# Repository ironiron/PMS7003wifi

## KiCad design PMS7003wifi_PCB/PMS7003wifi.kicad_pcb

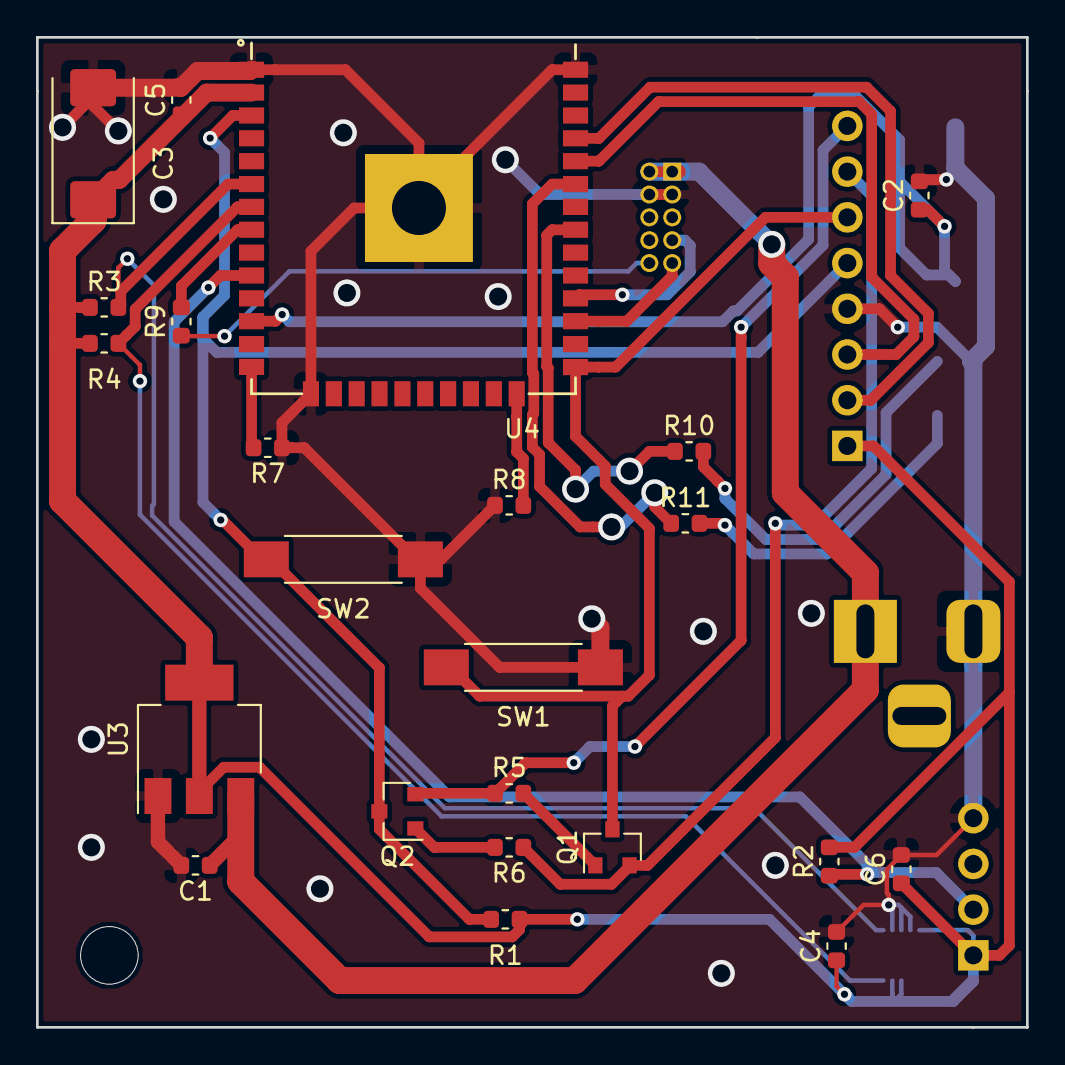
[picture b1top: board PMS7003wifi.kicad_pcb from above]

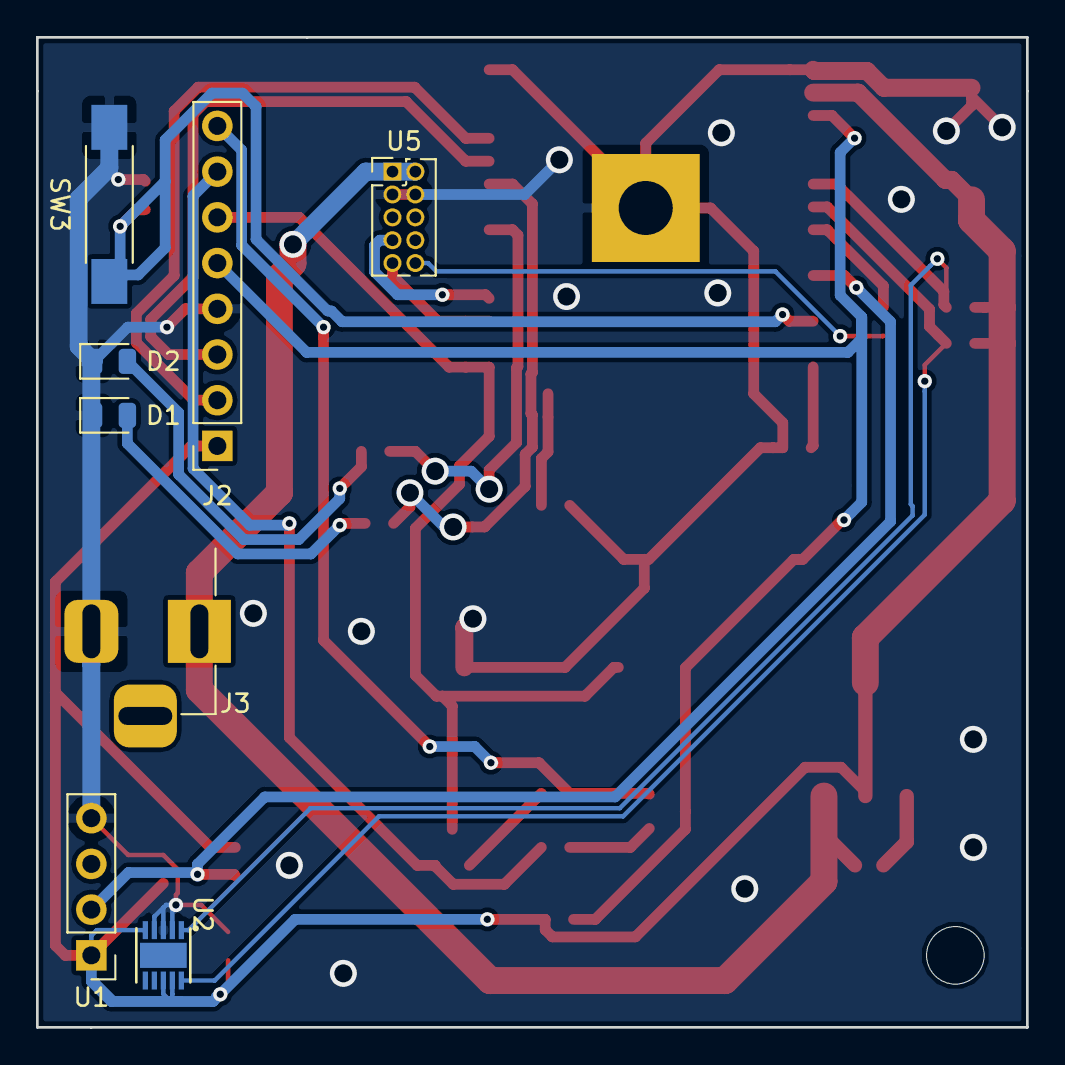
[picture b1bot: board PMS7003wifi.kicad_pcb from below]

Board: 2 copper layers, 55.0 x 55.0 mm, 32 parts (8 on the bottom side), 25 nets.

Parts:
 : MountingHole_3.2mm_M3
C1: 10u; C_0603_1608Metric
C2, C4, C5, C6: 100n; C_0603_1608Metric
C3: 470u; CP_EIA-7343-31_Kemet-D
D1, D2: RED; LED_0805_2012Metric
J2: Conn_01x06; PinSocket_1x08_P2.54mm_Vertical
J3: Jack-DC; BarrelJack_Horizontal
Q1, Q2: BC817; SOT-23
R1, R5, R6, R7, R8: 10K; R_0603_1608Metric
R2: 5K; R_0603_1608Metric
R3, R4: 2K2; R_0603_1608Metric
R9, R10, R11: 470; R_0603_1608Metric
SW1: DOWNLOAD_FLASH; SW_SPST_REED_CT05-XXXX-G1
SW2: EN(RST); SW_SPST_REED_CT05-XXXX-G1
SW3: wifi; SW_SPST_REED_CT05-XXXX-G1
U1: DHT11; PinHeader_1x04_P2.54mm_Vertical
U2: Si7013-A20; DFN10
U3: AP1117-33; SOT-223-3_TabPin2
U4: ESP32-WROOM; ESP32
U5: PMS7003; PinHeader_2x05_P1.27mm_Vertical

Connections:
+3V3: C3.1, C4.1, C5.1, C6.1, J2.1, R1.2, R2.2, R3.1, R4.1, U1.1, U2.5, U2.8, U2.9, U3.2, U4.2
+5V: C1.1, J3.1, U3.3, U5.1, U5.2
/DOWNLOAD_32: J2.6, Q1.3, SW1.1, U4.25
/DTR: J2.7, Q1.2, R6.1
/EN_32: J2.5, Q2.3, R1.1, SW2.1, U4.3
/MCU_RX: U4.27, U5.9
/MCU_TX: U4.28, U5.7
/ONEWIRE: R2.1, U1.2, U4.10
/RTS: J2.8, Q2.2, R5.1
/RX0_32: J2.3, U4.34
/SCLK: R4.2, U2.10, U4.7
/SDA: R3.2, U2.1, U4.6
/SET: R9.2, U4.8
/TX0_32: J2.2, U4.35
GND: C1.2, C2.2, C3.2, C4.2, C5.2, C6.2, D1.1, D2.1, J2.4, J3.2, R7.1, R8.1, SW1.2, SW2.2, SW3.1, U1.4, U2.2, U2.3, U2.4, U3.1, U4.1, U4.15, U4.38, U4.39, U5.3, U5.4
unnamed: C2.1, SW3.2, U4.12
unnamed: D1.2, R11.2
unnamed: D2.2, R10.2
unnamed: Q1.1, R5.2
unnamed: Q2.1, R6.2
unnamed: R7.2, U4.14
unnamed: R8.2, U4.24
unnamed: R9.1, U5.10
unnamed: R10.1, U4.31
unnamed: R11.1, U4.33

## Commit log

2019-06-20 initial release- added PCB schematic
2020-03-25 pcb update
2020-09-11 Initial software development begins
2021-01-08 part of pms driver done
